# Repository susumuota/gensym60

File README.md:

# gensym60

A redesign of the symmetrical 60% keyboard.

- 60% layout
- 7u space bar
- Split backspace
- Arrow keys (Up is mod-tap on the right shift)
- No split right shift

## Build firmware

```shell
git clone https://github.com/susumuota/gensym60.git

git clone https://github.com/vial-kb/vial-qmk.git
cd vial-qmk

# copy gensym60 directory to vial-qmk
rsync -av --delete ../gensym60/vial-qmk/keyboards/infinitemonkey/gensym60/ keyboards/infinitemonkey/gensym60/

RUNTIME="docker" SKIP_FLASHING_SUPPORT=1 util/docker_cmd.sh make infinitemonkey/gensym60:vial

ls -l infinitemonkey_gensym60_vial.bin
# -rwxr-xr-x 1 user group 37072 Jun 18 01:23 infinitemonkey_gensym60_vial.bin
```

## Flash firmware

Install `dfu-util` package.

```shell
brew install dfu-util
```

```shell
# unplug and plug the device pressing the dfu button
dfu-util -l
sudo dfu-util -a 0 -s 0x08000000:unprotect:force

# unplug and plug the device pressing the dfu button
dfu-util -l
sudo dfu-util -a 0 -s 0x08000000:mass-erase:force

# unplug and plug the device pressing the dfu button
dfu-util -l
sudo dfu-util -a 0 -s 0x08000000:leave -D infinitemonkey_gensym60_vial.bin
```

## References

- https://github.com/Unified-Daughterboard/UDB-C-JSH
- https://github.com/kkatano/bakeneko-60
- https://github.com/takishim/mikeneko65
- https://github.com/tominabox1/Le-Chiffre-Keyboard
- https://github.com/sporkus/le_chiffre_keyboard_stm32
- https://github.com/joe-scotto/scottokeebs/tree/main/Extras/ScottoModules/STM32F072CBT6
- https://www.st.com/resource/en/application_note/an4080-getting-started-with-stm32f0x1x2x8-hardware-development-stmicroelectronics.pdf
- https://www.st.com/en/evaluation-tools/32f072bdiscovery.html
- https://microfan.shop/products/stm32f072-mini-r1
- https://github.com/ShaneTWilliams/stm32-dev-board
- https://github.com/bennymeg/Fabrication-Toolkit
- https://github.com/Salicylic-acid3/KiCAD_FootPrint

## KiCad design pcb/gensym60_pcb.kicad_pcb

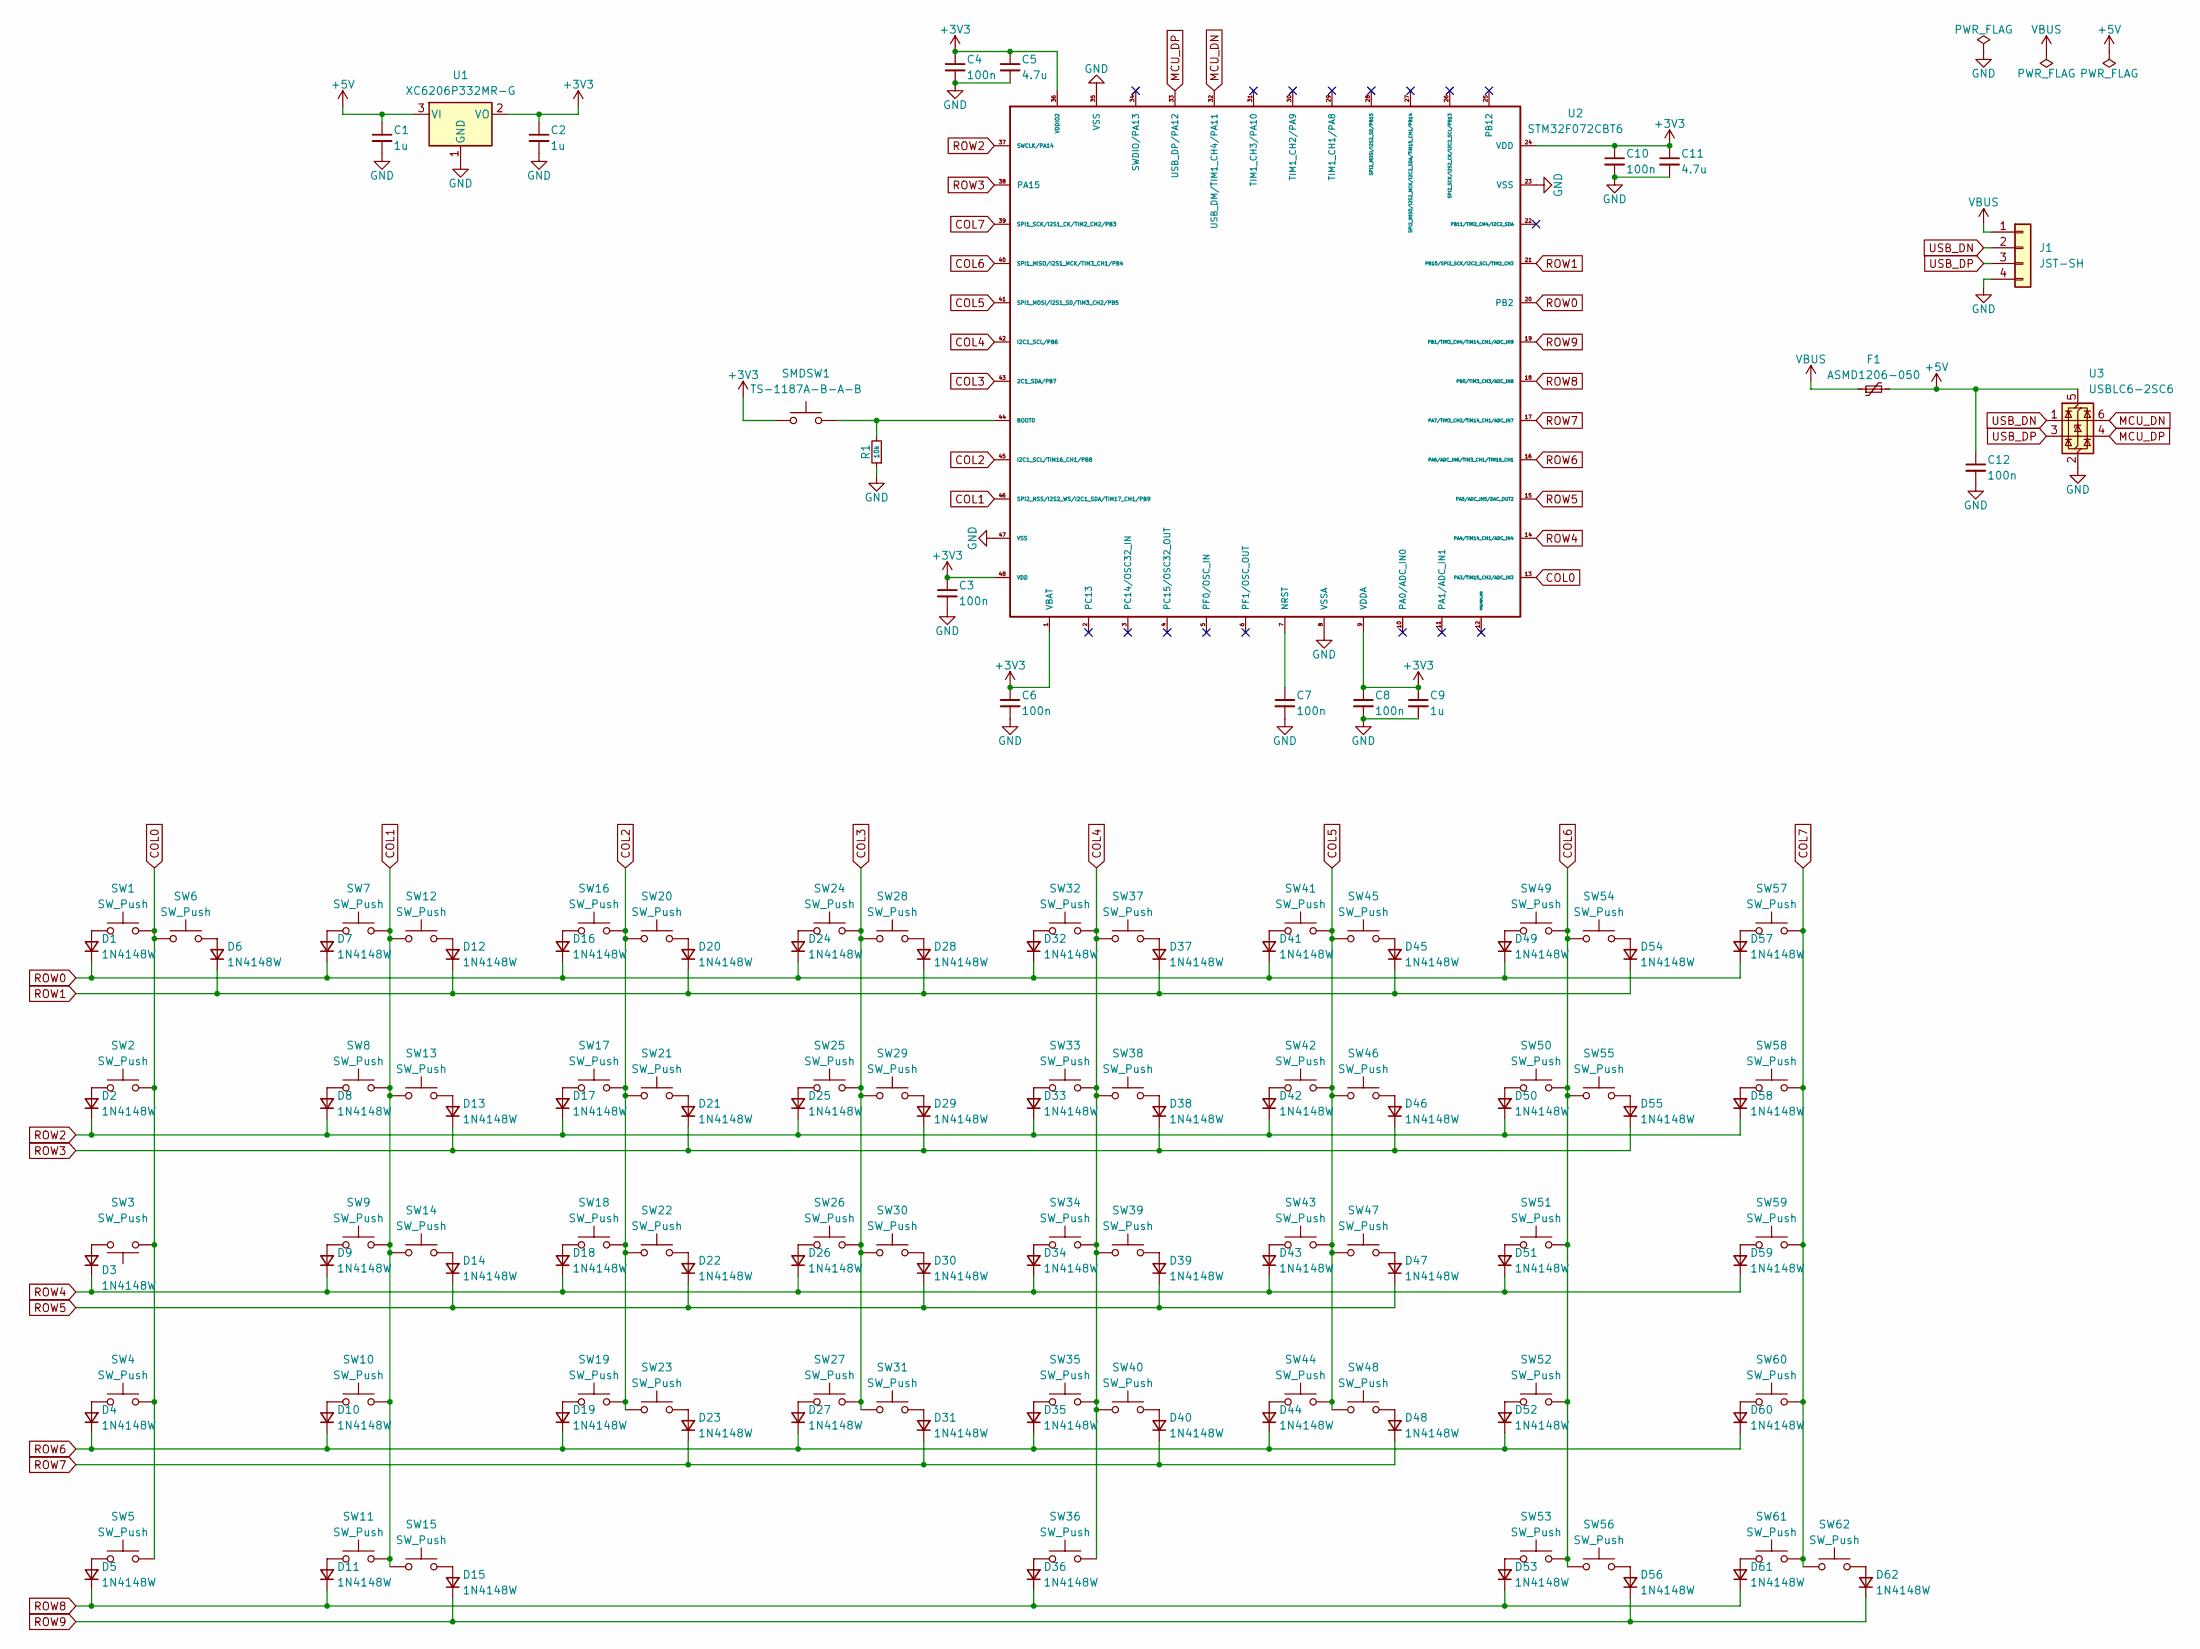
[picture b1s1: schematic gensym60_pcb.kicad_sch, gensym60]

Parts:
C1, C2, C9: 1u; C_0402_1005Metric; MFR.Part # CL05A105KA5NQNC; LCSC PN C52923
C3, C4, C6, C7, C8, C10, C12: 100n; C_0402_1005Metric; MFR.Part # CL05B104KO5NNNC; LCSC PN C1525
C5, C11: 4.7u; C_0402_1005Metric; MFR.Part # CL05A475MP5NRNC; LCSC PN C23733
D1, D2, D3, D4, D5, D6, D7, D8, D9, D10, D11, D12, D13, D14, D15, D16, D17, D18, D19, D20, D21, D22, D23, D24, D25, D26, D27, D28, D29, D30, D31, D32, D33, D34, D35, D36, D37, D38, D39, D40, D41, D42, D43, D44, D45, D46, D47, D48, D49, D50, D51, D52, D53, D54, D55, D56, D57, D58, D59, D60, D61, D62: 1N4148W; D_SOD-123; MFR.Part # 1N4148W; LCSC PN C81598
F1: ASMD1206-050; Fuse_1206_3216Metric; MFR.Part # ASMD1206-050; LCSC PN C135338
J1: JST-SH; JST_SH_SM04B-SRSS-TB_1x04-1MP_P1.00mm_Horizontal; MFR.Part # SM04B-SRSS-TB(LF)(SN); LCSC PN C160404
R1: 10k; R_0402_1005Metric; MFR.Part # 0402WGF1002TCE; LCSC PN C25744
SMDSW1: TS-1187A-B-A-B; SW_Push_1P1T_XKB_TS-1187A; MFR.Part # TS-1187A-B-A-B; LCSC PN C318884
SW1, SW6, SW7, SW8, SW9, SW10, SW12, SW13, SW14, SW16, SW17, SW18, SW19, SW20, SW21, SW22, SW23, SW24, SW25, SW26, SW27, SW28, SW29, SW30, SW31, SW32, SW33, SW34, SW35, SW37, SW38, SW39, SW40, SW41, SW42, SW43, SW44, SW45, SW46, SW47, SW48, SW49, SW50, SW51, SW52, SW54, SW55, SW56, SW57, SW61, SW62: SW_Push; CherryMX_Hotswap_1u; MFR.Part # CPG151101S11-16; LCSC PN C41430893
SW2, SW58: SW_Push; CherryMX_Hotswap_1.5u; MFR.Part # CPG151101S11-16; LCSC PN C41430893
SW3: SW_Push; CherryMX_Hotswap_1.75u; MFR.Part # CPG151101S11-16; LCSC PN C41430893
SW4, SW59: SW_Push; CherryMX_Hotswap_2.25u; MFR.Part # CPG151101S11-16; LCSC PN C41430893
SW5, SW11, SW15, SW53: SW_Push; CherryMX_Hotswap_1.25u; MFR.Part # CPG151101S11-16; LCSC PN C41430893
SW36: SW_Push; CherryMX_Hotswap_7u_Rev; MFR.Part # CPG151101S11-16; LCSC PN C41430893
SW60: SW_Push; CherryMX_Hotswap_2.75u; MFR.Part # CPG151101S11-16; LCSC PN C41430893
U1: XC6206P332MR-G; SOT-23-3; MFR.Part # XC6206P332MR-G; LCSC PN C5446
U2: STM32F072CBT6; LQFP-48_7x7mm_P0.5mm; MFR.Part # STM32F072CBT6; LCSC PN C81720
U3: USBLC6-2SC6; SOT-23-6; MFR.Part # USBLC6-2SC6; LCSC PN C7519

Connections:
+3V3: C2.1, C3.1, C4.1, C5.1, C6.1, C8.1, C9.1, C10.1, C11.1, SMDSW1.1, U1.2 (VO), U2.1 (VBAT), U2.9 (VDDA), U2.24 (VDD), U2.36 (VDDIO2), U2.48 (VDD)
+5V: C1.1, C12.1, F1.2, U1.3 (VI), U3.5 (VBUS)
COL0: SW1.2, SW2.2, SW3.1, SW4.2, SW5.2, SW6.1, U2.13 (PA3/TIM15_CH2/ADC_IN3)
COL1: SW7.2, SW8.2, SW9.2, SW10.2, SW11.2, SW12.1, SW13.1, SW14.1, SW15.1, U2.46 (SPI2_NSS/I2S2_WS/I2C1_SDA/TIM17_CH1/PB9)
COL2: SW16.2, SW17.2, SW18.2, SW19.2, SW20.1, SW21.1, SW22.1, SW23.1, U2.45 (I2C1_SCL/TIM16_CH1/PB8)
COL3: SW24.2, SW25.2, SW26.2, SW27.2, SW28.1, SW29.1, SW30.1, SW31.1, U2.43 (2C1_SDA/PB7)
COL4: SW32.2, SW33.2, SW34.2, SW35.2, SW36.2, SW37.1, SW38.1, SW39.1, SW40.1, U2.42 (I2C1_SCL/PB6)
COL5: SW41.2, SW42.2, SW43.2, SW44.2, SW45.1, SW46.1, SW47.1, SW48.1, U2.41 (SPI1_MOSI/I2S1_SD/TIM3_CH2/PB5)
COL6: SW49.2, SW50.2, SW51.2, SW52.2, SW53.2, SW54.1, SW55.1, SW56.1, U2.40 (SPI1_MISO/I2S1_MCK/TIM3_CH1/PB4)
COL7: SW57.2, SW58.2, SW59.2, SW60.2, SW61.2, SW62.1, U2.39 (SPI1_SCK/I2S1_CK/TIM2_CH2/PB3)
GND: C1.2, C2.2, C3.2, C4.2, C5.2, C6.2, C7.2, C8.2, C9.2, C10.2, C11.2, C12.2, J1.4, R1.1, U1.1 (GND), U2.8 (VSSA), U2.23 (VSS), U2.35 (VSS), U2.47 (VSS), U3.2 (GND)
MCU_DN: U2.32 (USB_DM/TIM1_CH4/PA11), U3.6 (I/O1)
MCU_DP: U2.33 (USB_DP/PA12), U3.4 (I/O2)
unnamed: D1.2 (A), SW1.1
unnamed: D2.2 (A), SW2.1
unnamed: D3.2 (A), SW3.2
unnamed: D4.2 (A), SW4.1
unnamed: D5.2 (A), SW5.1
unnamed: D6.2 (A), SW6.2
unnamed: D7.2 (A), SW7.1
unnamed: D8.2 (A), SW8.1
unnamed: D9.2 (A), SW9.1
unnamed: D10.2 (A), SW10.1
unnamed: D11.2 (A), SW11.1
unnamed: D12.2 (A), SW12.2
unnamed: D13.2 (A), SW13.2
unnamed: D14.2 (A), SW14.2
unnamed: D15.2 (A), SW15.2
unnamed: D16.2 (A), SW16.1
unnamed: D17.2 (A), SW17.1
unnamed: D18.2 (A), SW18.1
unnamed: D19.2 (A), SW19.1
unnamed: D20.2 (A), SW20.2
unnamed: D21.2 (A), SW21.2
unnamed: D22.2 (A), SW22.2
unnamed: D23.2 (A), SW23.2
unnamed: D24.2 (A), SW24.1
unnamed: D25.2 (A), SW25.1
unnamed: D26.2 (A), SW26.1
unnamed: D27.2 (A), SW27.1
unnamed: D28.2 (A), SW28.2
unnamed: D29.2 (A), SW29.2
unnamed: D30.2 (A), SW30.2
unnamed: D31.2 (A), SW31.2
unnamed: D32.2 (A), SW32.1
unnamed: D33.2 (A), SW33.1
unnamed: D34.2 (A), SW34.1
unnamed: D35.2 (A), SW35.1
unnamed: D36.2 (A), SW36.1
unnamed: D37.2 (A), SW37.2
unnamed: D38.2 (A), SW38.2
unnamed: D39.2 (A), SW39.2
unnamed: D40.2 (A), SW40.2
unnamed: D41.2 (A), SW41.1
unnamed: D42.2 (A), SW42.1
unnamed: D43.2 (A), SW43.1
unnamed: D44.2 (A), SW44.1
unnamed: D45.2 (A), SW45.2
unnamed: D46.2 (A), SW46.2
unnamed: D47.2 (A), SW47.2
unnamed: D48.2 (A), SW48.2
unnamed: D49.2 (A), SW49.1
unnamed: D50.2 (A), SW50.1
unnamed: D51.2 (A), SW51.1
unnamed: D52.2 (A), SW52.1
unnamed: D53.2 (A), SW53.1
unnamed: D54.2 (A), SW54.2
unnamed: D55.2 (A), SW55.2
unnamed: D56.2 (A), SW56.2
unnamed: D57.2 (A), SW57.1
unnamed: D58.2 (A), SW58.1
unnamed: D59.2 (A), SW59.1
unnamed: D60.2 (A), SW60.1
unnamed: D61.2 (A), SW61.1
unnamed: D62.2 (A), SW62.2
unnamed: R1.2, SMDSW1.2, U2.44 (BOOT0)
unnamed: C7.1, U2.7 (NRST)
ROW0: D1.1 (K), D7.1 (K), D16.1 (K), D24.1 (K), D32.1 (K), D41.1 (K), D49.1 (K), D57.1 (K), U2.20 (PB2)
ROW1: D6.1 (K), D12.1 (K), D20.1 (K), D28.1 (K), D37.1 (K), D45.1 (K), D54.1 (K), U2.21 (PB10/SPI2_SCK/I2C2_SCL/TIM2_CH3)
ROW2: D2.1 (K), D8.1 (K), D17.1 (K), D25.1 (K), D33.1 (K), D42.1 (K), D50.1 (K), D58.1 (K), U2.37 (SWCLK/PA14)
ROW3: D13.1 (K), D21.1 (K), D29.1 (K), D38.1 (K), D46.1 (K), D55.1 (K), U2.38 (PA15)
ROW4: D3.1 (K), D9.1 (K), D18.1 (K), D26.1 (K), D34.1 (K), D43.1 (K), D51.1 (K), D59.1 (K), U2.14 (PA4/TIM14_CH1/ADC_IN4)
ROW5: D14.1 (K), D22.1 (K), D30.1 (K), D39.1 (K), D47.1 (K), U2.15 (PA5/ADC_IN5/DAC_OUT2)
ROW6: D4.1 (K), D10.1 (K), D19.1 (K), D27.1 (K), D35.1 (K), D44.1 (K), D52.1 (K), D60.1 (K), U2.16 (PA6/ADC_IN6/TIM3_CH1/TIM16_CH1)
ROW7: D23.1 (K), D31.1 (K), D40.1 (K), D48.1 (K), U2.17 (PA7/TIM3_CH2/TIM14_CH1/ADC_IN7)
ROW8: D5.1 (K), D11.1 (K), D36.1 (K), D53.1 (K), D61.1 (K), U2.18 (PB0/TIM3_CH3/ADC_IN8)
ROW9: D15.1 (K), D56.1 (K), D62.1 (K), U2.19 (PB1/TIM3_CH4/TIM14_CH1/ADC_IN9)
USB_DN: J1.2, U3.1 (I/O1)
USB_DP: J1.3, U3.3 (I/O2)
VBUS: F1.1, J1.1

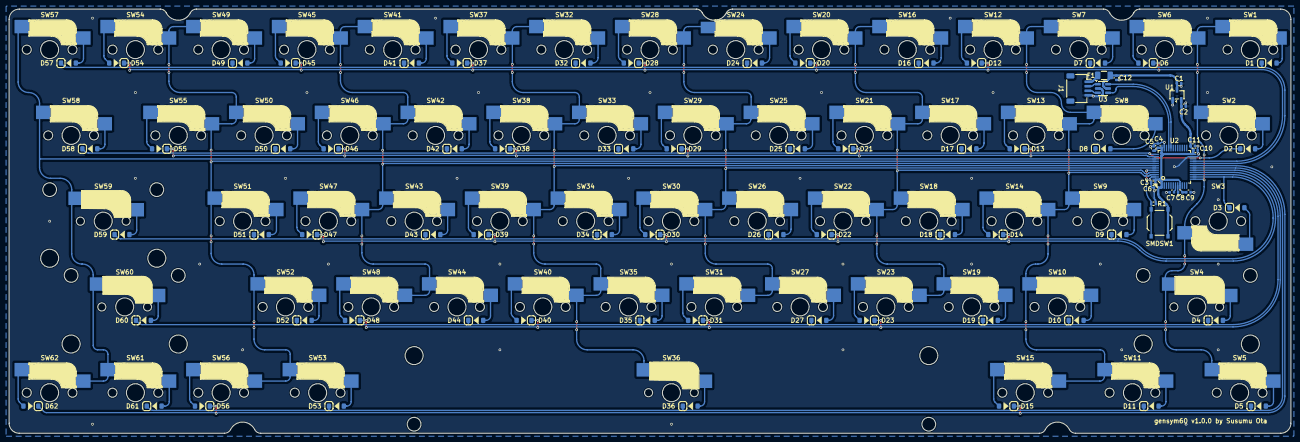
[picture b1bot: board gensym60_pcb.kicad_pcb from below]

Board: 2 copper layers, 284.7 x 94.2 mm, 143 parts (81 on the bottom side), 90 nets.

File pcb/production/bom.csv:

Designator,Footprint,Quantity,Value,LCSC Part #
"C1, C2, C9",0402,3,1u,C52923
"C10, C12, C3, C4, C6, C7, C8",0402,7,100n,C1525
"C11, C5",0402,2,4.7u,C23733
"D1, D10, D11, D12, D13, D14, D15, D16, D17, D18, D19, D2, D20, D21, D22, D23, D24, D25, D26, D27, D28, D29, D3, D30, D31, D32, D33, D34, D35, D36, D37, D38, D39, D4, D40, D41, D42, D43, D44, D45, D46, D47, D48, D49, D5, D50, D51, D52, D53, D54, D55, D56, D57, D58, D59, D6, D60, D61, D62, D7, D8, D9",D_SOD-123,62,1N4148W,C81598
F1,1206,1,ASMD1206-050,C135338
J1,JST_SH_SM04B-SRSS-TB_1x04-1MP_P1.00mm_Horizontal,1,JST-SH,C160404
R1,0402,1,10k,C25744
SMDSW1,SW_Push_1P1T_XKB_TS-1187A,1,TS-1187A-B-A-B,C318884
"SW1, SW10, SW12, SW13, SW14, SW16, SW17, SW18, SW19, SW20, SW21, SW22, SW23, SW24, SW25, SW26, SW27, SW28, SW29, SW30, SW31, SW32, SW33, SW34, SW35, SW37, SW38, SW39, SW40, SW41, SW42, SW43, SW44, SW45, SW46, SW47, SW48, SW49, SW50, SW51, SW52, SW54, SW55, SW56, SW57, SW6, SW61, SW62, SW7, SW8, SW9",CherryMX_Hotswap_1u,51,SW_Push,C41430893
"SW11, SW15, SW5, SW53",CherryMX_Hotswap_1.25u,4,SW_Push,C41430893
"SW2, SW58",CherryMX_Hotswap_1.5u,2,SW_Push,C41430893
SW3,CherryMX_Hotswap_1.75u,1,SW_Push,C41430893
SW36,CherryMX_Hotswap_7u_Rev,1,SW_Push,C41430893
"SW4, SW59",CherryMX_Hotswap_2.25u,2,SW_Push,C41430893
SW60,CherryMX_Hotswap_2.75u,1,SW_Push,C41430893
U1,SOT-23-3,1,XC6206P332MR-G,C5446
U2,LQFP-48_7x7mm_P0.5mm,1,STM32F072CBT6,C81720
U3,SOT-23-6,1,USBLC6-2SC6,C7519

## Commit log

2025-10-20 feat: initial commit
2025-10-20 feat: add usb-c daughter board
2025-10-20 feat: add key matrix
2025-10-20 chore: ignore .vscode
2025-10-22 feat: place switches
2025-10-25 feat: connect switches
2025-10-26 feat: add fuse and esd
2025-10-31 feat: move mcu
2025-10-31 feat: add plate files
2025-12-06 feat: tweak design for production
2026-06-05 chore: add production fabrication outputs for ordering
2026-06-05 chore: ignore .claude and clarify directory patterns in gitignore
2026-06-05 chore: add MIT license
2026-06-16 chore: ignore history directory
2026-06-16 chore: update plate fabrication files
2026-06-16 feat: add gensym60 vial qmk files
2026-06-18 chore: standardize gensym60 naming
2026-06-18 chore: rename fabrication archives
2026-06-18 docs: add firmware build and flash instructions
2026-06-18 docs: standardize gensym60 heading
